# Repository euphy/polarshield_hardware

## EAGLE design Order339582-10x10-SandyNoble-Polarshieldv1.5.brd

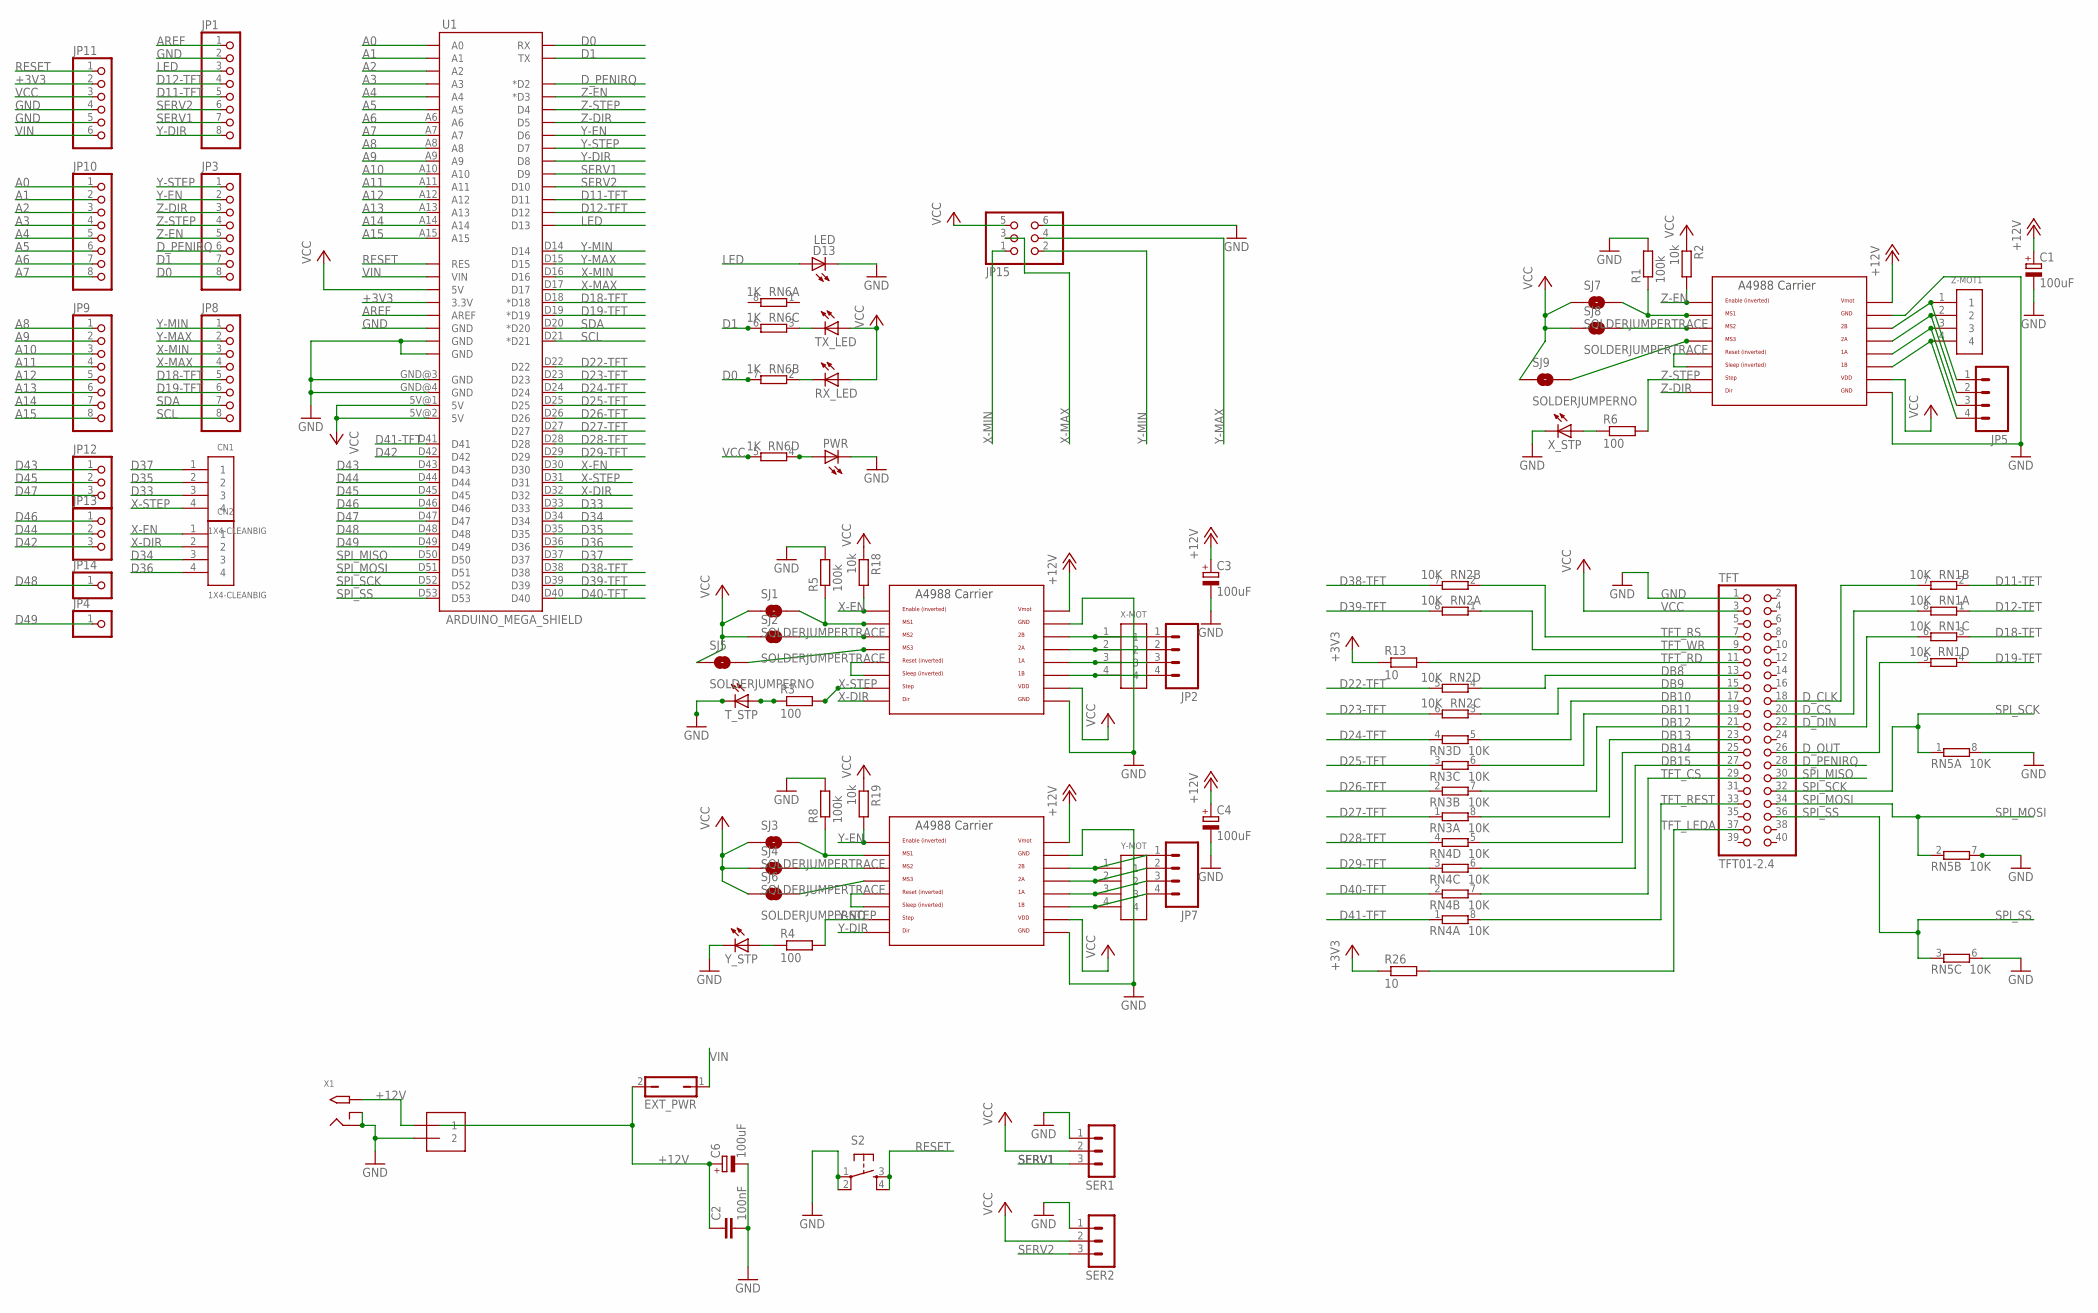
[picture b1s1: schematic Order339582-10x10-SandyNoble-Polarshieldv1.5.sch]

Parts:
C1, C3, C4, C6: 100uF; 153CLV-0605
C2: 100nF; C0805
CN1, CN2: 1X4-CLEANBIG; 1X04-CLEANBIG
D13: LED; CHIP-LED0805
EXT_PWR: JP1Q; JP1
J1: 1X2-3.5MM
JP1, JP3, JP8, JP9, JP10: PINHD-1X8CLEANBIG; 1X08-CLEANBIG
JP2, JP5, JP7: M04SCREW; SCREWTERMINAL-3.5MM-4
JP4, JP14: PINHD-1X1CB; 1X01-CLEANBIG
JP11: PINHD-1X6CB; 1X06-CLEANBIG
JP12, JP13: PINHD-1X3CB; 1X03-CLEANBIG
JP15: PINHD-2X3; 2X03
PWR: LEDCHIP-LED0805; CHIP-LED0805
R1, R5, R8: 100k; R0805
R2, R18, R19: 10k; R0805
R3, R4, R6: 100; R0805
R13, R26: 10; R0805
RN1, RN2, RN3, RN4, RN5: 10K; EXBS8V
RN6: 1K; EXBS8V
RX_LED: LEDCHIP-LED0805; CHIP-LED0805
S2: TAC_SWITCHPTH; TACTILE-PTH
SER1, SER2: 3PIN-HEADER
SJ1, SJ2, SJ3, SJ4, SJ7, SJ8: SOLDERJUMPERTRACE; SJ_2S-TRACE
SJ5, SJ6, SJ9: SOLDERJUMPERNO; SJ_2S-NO
TFT: TFT01-2.4
TX_LED: LEDCHIP-LED0805; CHIP-LED0805
T_STP: LEDCHIP-LED0805; CHIP-LED0805
U1: ARDUINO_MEGA_SHIELD
U$1, U$6, U$7: A4988BREAKOUT
X1: 2.1MMJACKTHM; PJ-102A
X-MOT: 1X4-BIG; 1X04-BIG
X_STP: LEDCHIP-LED0805; CHIP-LED0805
Y-MOT: 1X4-BIG; 1X04-BIG
Y_STP: LEDCHIP-LED0805; CHIP-LED0805
Z-MOT1: 1X4-BIG; 1X04-BIG

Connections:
+3V3: JP11.2, R13.1, R26.1, U1.3.3V
+12V: C1.+, C2.1, C3.+, C4.+, C6.+, EXT_PWR.2, J1.1, U$1.VMOT, U$6.VMOT, U$7.VMOT, X1.TIP
A0: JP10.1, U1.A0
A1: JP10.2, U1.A1
A2: JP10.3, U1.A2
A3: JP10.4, U1.A3
A4: JP10.5, U1.A4
A5: JP10.6, U1.A5
A6: JP10.7, U1.A6
A7: JP10.8, U1.A7
A8: JP9.1, U1.A8
A9: JP9.2, U1.A9
A10: JP9.3, U1.A10
A11: JP9.4, U1.A11
A12: JP9.5, U1.A12
A13: JP9.6, U1.A13
A14: JP9.7, U1.A14
A15: JP9.8, U1.A15
AREF: JP1.1, U1.AREF
D0: JP3.8, RN6.7 (2), U1.RX
D1: JP3.7, RN6.6 (2), U1.TX
D11-TFT: JP1.5, RN1.2 (1), U1.D11
D12-TFT: JP1.4, RN1.1, U1.D12
D18-TFT: JP8.5, RN1.3 (1), U1.D18 (*D18)
D19-TFT: JP8.6, RN1.4 (1), U1.D19 (*D19)
D22-TFT: RN2.5 (2), U1.D22
D23-TFT: RN2.6 (2), U1.D23
D24-TFT: RN3.4 (1), U1.D24
D25-TFT: RN3.3 (1), U1.D25
D26-TFT: RN3.2 (1), U1.D26
D27-TFT: RN3.1, U1.D27
D28-TFT: RN4.4 (1), U1.D28
D29-TFT: RN4.3 (1), U1.D29
D33: CN1.3, U1.D33
D34: CN2.3, U1.D34
D35: CN1.2, U1.D35
D36: CN2.4, U1.D36
D37: CN1.1, U1.D37
D38-TFT: RN2.7 (2), U1.D38
D39-TFT: RN2.8 (2), U1.D39
D40-TFT: RN4.2 (1), U1.D40
D41-TFT: RN4.1, U1.D41
D42: JP13.3, U1.D42
D43: JP12.1, U1.D43
D44: JP13.2, U1.D44
D45: JP12.2, U1.D45
D46: JP13.1, U1.D46
D47: JP12.3, U1.D47
D48: JP14.1, U1.D48
D49: JP4.1, U1.D49
DB8: RN2.4 (1), TFT.13
DB9: RN2.3 (1), TFT.15
DB10: RN3.5 (2), TFT.17
DB11: RN3.6 (2), TFT.19
DB12: RN3.7 (2), TFT.21
DB13: RN3.8 (2), TFT.23
DB14: RN4.5 (2), TFT.25
DB15: RN4.6 (2), TFT.27
D_CLK: RN1.7 (2), TFT.18
D_CS: RN1.8 (2), TFT.20
D_DIN: RN1.6 (2), TFT.22
D_OUT: RN1.5 (2), TFT.26
D_PENIRQ: JP3.6, TFT.28, U1.D2 (*D2)
GND: C1.-, C2.2, C3.-, C4.-, C6.-, D13.C, J1.2, JP1.2, JP11.4, JP11.5, JP15.6, PWR.C, R1.2, R5.2, R8.2, RN5.6 (2), RN5.7 (2), RN5.8 (2), S2.1, S2.2, SER1.1, SER2.1, TFT.1, T_STP.C, U1.GND@0 (GND), U1.GND@1 (GND), U1.GND@2 (GND), U1.GND@3 (GND), U1.GND@4 (GND), U$1.GND, U$1.GND@0 (GND), U$6.GND, U$6.GND@0 (GND), U$7.GND, U$7.GND@0 (GND), X1.RING, X1.RING_SW, X_STP.C, Y_STP.C
LED: D13.A, JP1.3, U1.D13
unnamed: U$6.RST, U$6.SLP (SLEEP)
unnamed: PWR.A, RN6.4 (1)
unnamed: R5.1, SJ1.2, U$6.MS1
unnamed: JP5.1, U$1.2B, Z-MOT1.1
unnamed: JP5.2, U$1.2A, Z-MOT1.2
unnamed: JP5.3, U$1.1A, Z-MOT1.3
unnamed: JP5.4, U$1.1B, Z-MOT1.4
unnamed: U$1.RST, U$1.SLP (SLEEP)
unnamed: R1.1, SJ7.2, U$1.MS1
unnamed: SJ2.2, U$6.MS2
unnamed: SJ8.2, U$1.MS2
unnamed: SJ5.2, U$6.MS3
unnamed: U$7.RST, U$7.SLP (SLEEP)
unnamed: SJ9.2, U$1.MS3
unnamed: RN6.2 (1), RX_LED.C
unnamed: RN6.3 (1), TX_LED.C
unnamed: SJ4.2, U$7.MS2
unnamed: R4.1, Y_STP.A
unnamed: R6.1, X_STP.A
unnamed: JP2.1, U$6.2B, X-MOT.1
unnamed: JP2.2, U$6.2A, X-MOT.2
unnamed: R3.1, T_STP.A
unnamed: JP2.3, U$6.1A, X-MOT.3
unnamed: JP2.4, U$6.1B, X-MOT.4
unnamed: JP7.1, U$7.2B, Y-MOT.1
unnamed: JP7.2, U$7.2A, Y-MOT.2
unnamed: JP7.3, U$7.1A, Y-MOT.3
unnamed: SJ6.2, U$7.MS3
unnamed: R8.1, SJ3.2, U$7.MS1
unnamed: JP7.4, U$7.1B, Y-MOT.4
RESET: JP11.1, S2.3, S2.4, U1.RES
SCL: JP8.8, U1.D21 (*D21)
SDA: JP8.7, U1.D20 (*D20)
SERV1: JP1.7, SER1.3, U1.D9
SERV2: JP1.6, SER2.3, U1.D10
SPI_MISO: TFT.30, U1.D50
SPI_MOSI: RN5.2 (1), TFT.34, U1.D51
SPI_SCK: RN5.1, TFT.32, U1.D52
SPI_SS: RN5.3 (1), TFT.36, U1.D53
TFT_CS: RN4.7 (2), TFT.29
TFT_LEDA: R26.2, TFT.37
TFT_RD: R13.2, TFT.11
TFT_REST: RN4.8 (2), TFT.33
TFT_RS: RN2.2 (1), TFT.7
TFT_WR: RN2.1, TFT.9
VCC: JP11.3, JP15.5, R2.1, R18.1, R19.1, RN6.5 (2), RX_LED.A, SER1.2, SER2.2, SJ1.1, SJ2.1, SJ3.1, SJ4.1, SJ5.1, SJ6.1, SJ7.1, SJ8.1, SJ9.1, TFT.3, TX_LED.A, U1.5V@0 (5V), U1.5V@1 (5V), U1.5V@2 (5V), U$1.VDD, U$6.VDD, U$7.VDD
VIN: EXT_PWR.1, JP11.6, U1.VIN
X-DIR: CN2.2, U1.D32, U$6.DIR
X-EN: CN2.1, R18.2, U1.D30, U$6.EN
X-MAX: JP8.4, JP15.3, U1.D17
X-MIN: JP8.3, JP15.1, U1.D16
X-STEP: CN1.4, R3.2, U1.D31, U$6.STEP
Y-DIR: JP1.8, U1.D8, U$7.DIR
Y-EN: JP3.2, R19.2, U1.D6, U$7.EN
Y-MAX: JP8.2, JP15.4, U1.D15
Y-MIN: JP8.1, JP15.2, U1.D14
Y-STEP: JP3.1, R4.2, U1.D7, U$7.STEP
Z-DIR: JP3.3, U1.D5, U$1.DIR
Z-EN: JP3.5, R2.2, U1.D3 (*D3), U$1.EN
Z-STEP: JP3.4, R6.2, U1.D4, U$1.STEP

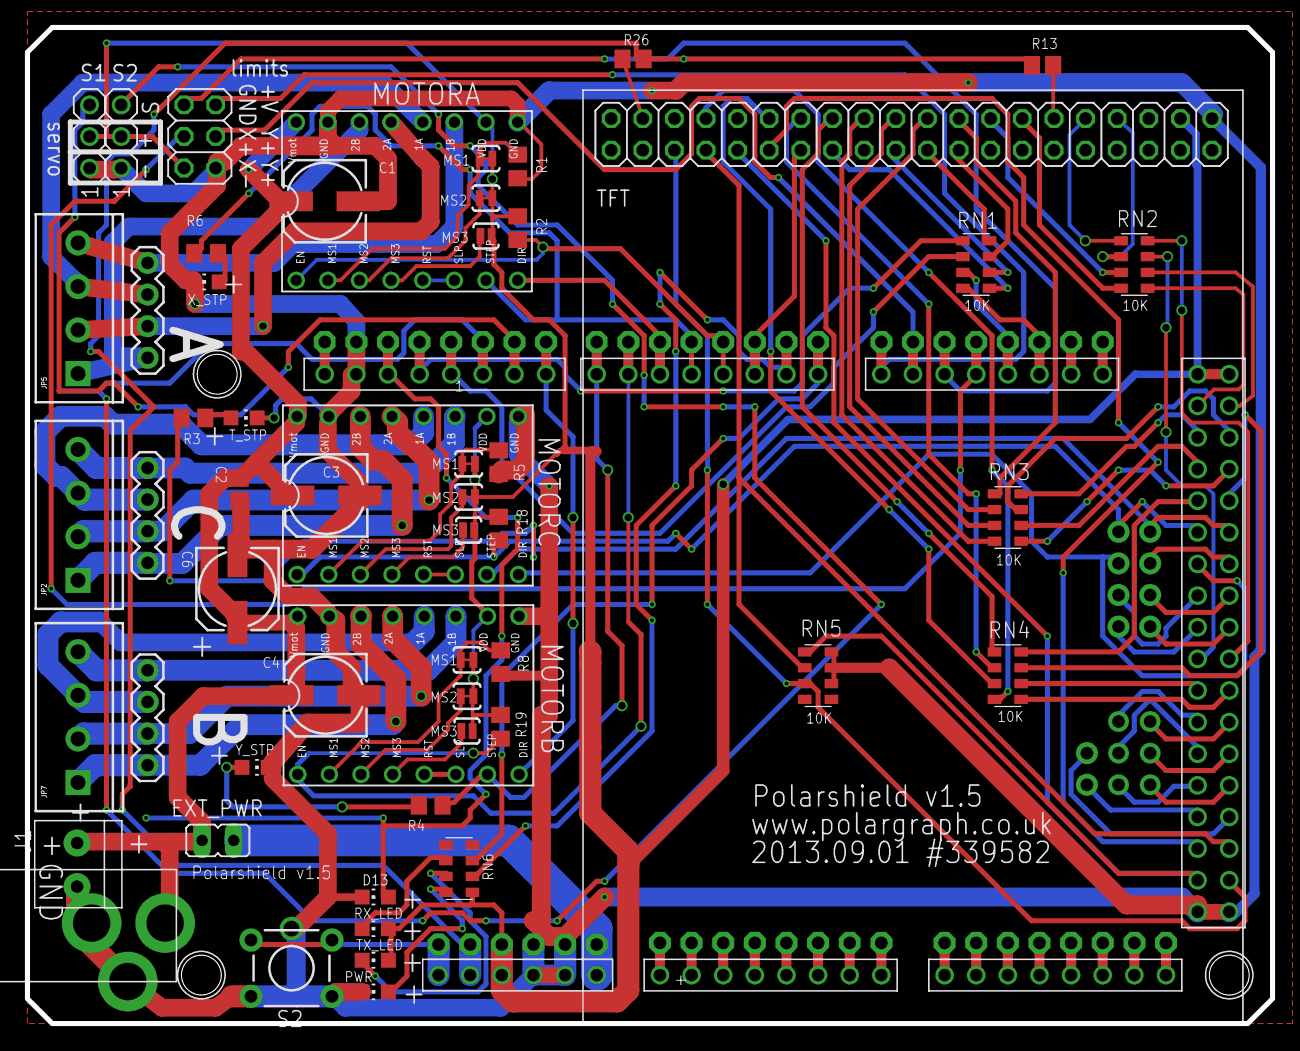
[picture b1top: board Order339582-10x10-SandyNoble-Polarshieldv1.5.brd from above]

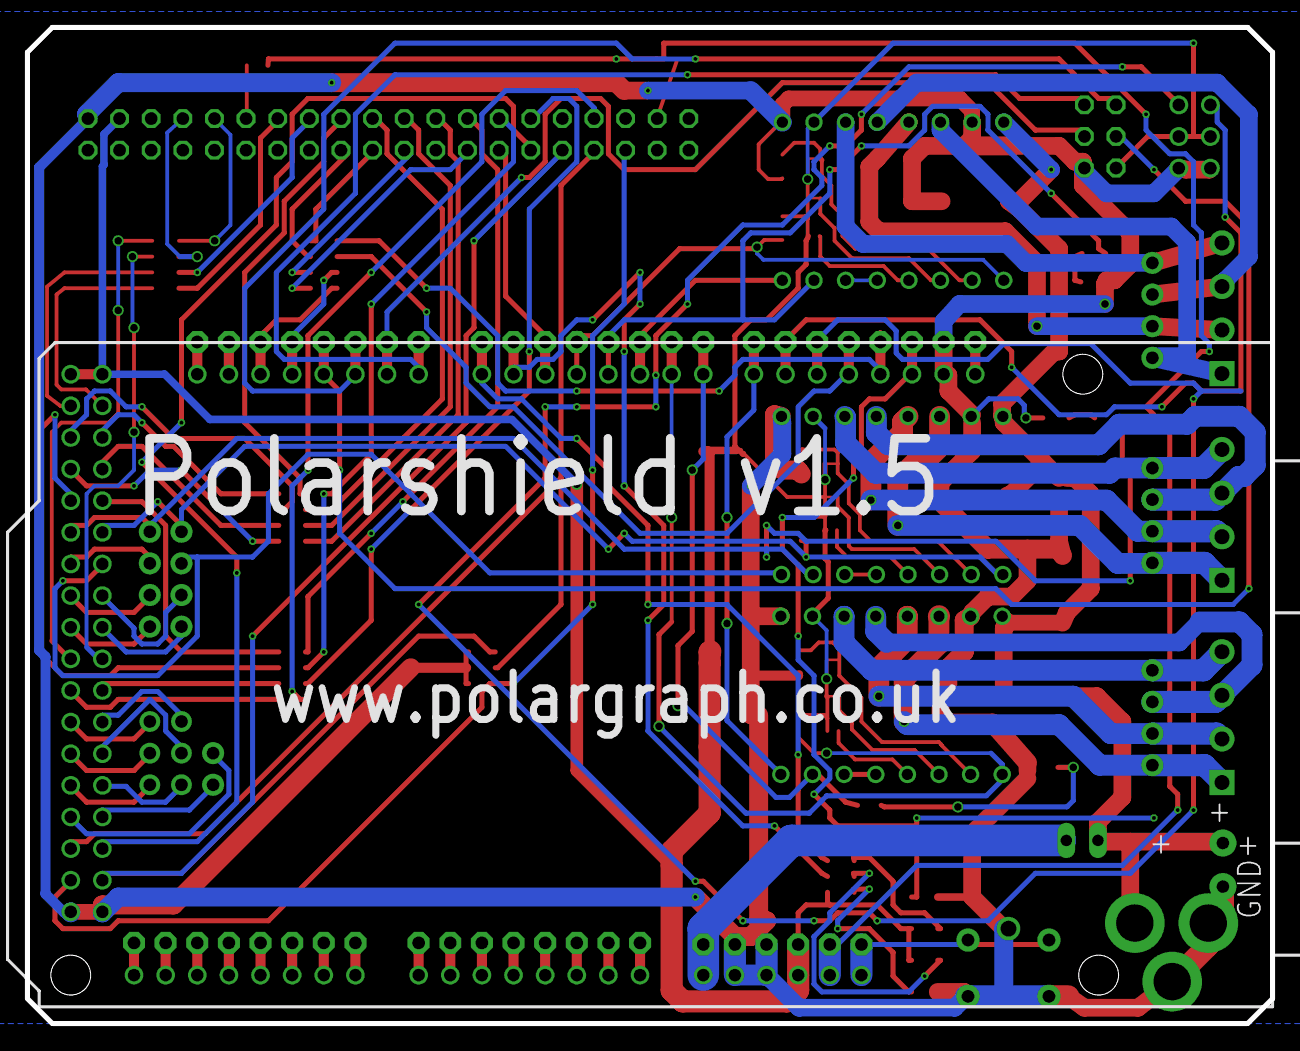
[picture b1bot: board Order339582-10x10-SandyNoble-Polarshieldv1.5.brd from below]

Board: 2 copper layers, 100.0 x 80.0 mm, 68 parts (2 on the bottom side), 125 nets.
